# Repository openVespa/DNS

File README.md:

A wifi based EGT, CHT, RPM, Speed monitor board. Works on 6vac and 12vac systems. No need for a battery. It works with iOS and android, or really anything with wifi. The goal is to keep the size reasonable and the total build price under $25. It is based around the ESP8266 wifi SoC. RPM is calculated off the AC from the stator, using an NCV1124 for zero crossing. The EGT is a Ktype thermocouple and the CHT is a TrailTech. The EGT and CHT signals are converted using an ADS1120 ADC SPI device. To make it easy to modify, I'm doing all the firmware in Arduino.

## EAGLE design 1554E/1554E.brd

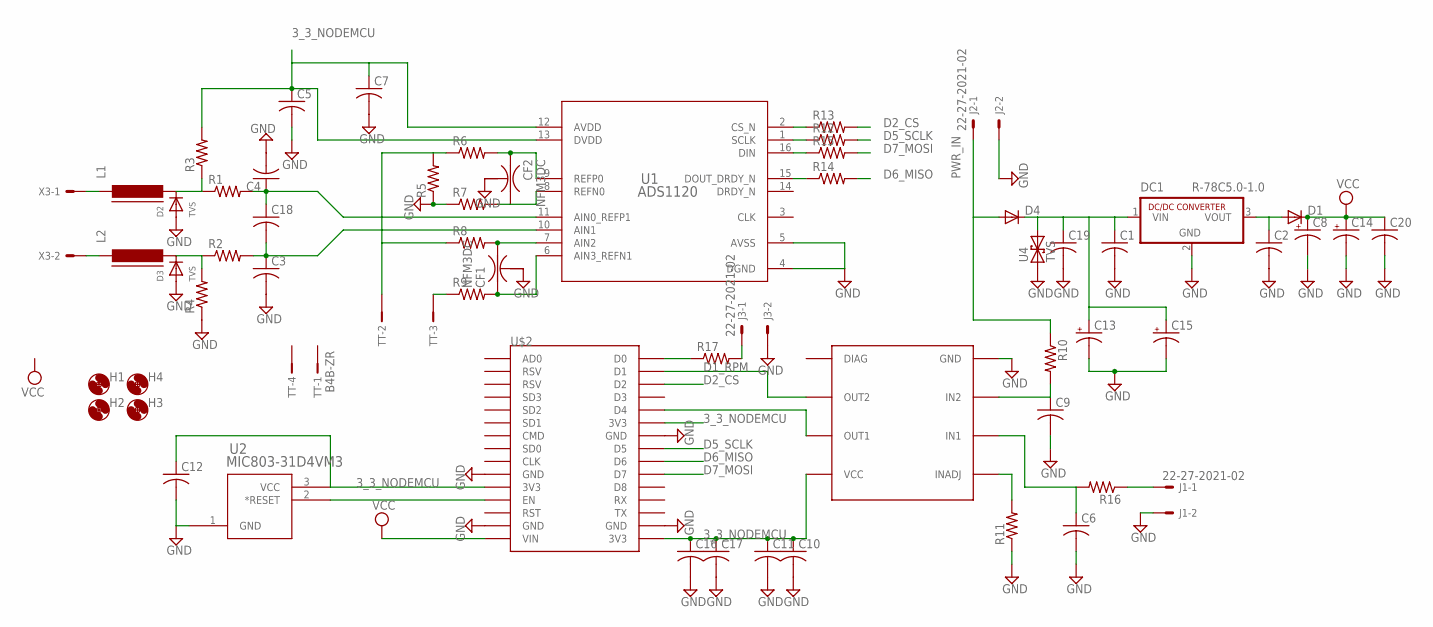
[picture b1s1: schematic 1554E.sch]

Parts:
C1, C2, C3, C4, C5, C6, C7, C9, C10, C11, C12, C18: C-USC0805K; C0805K
C8, C13, C14: CPOL-USE2.5-5; E2,5-5
C15: CPOL-USE7.5-16; E7,5-16
C16, C17, C19, C20: C-USC1206K; C1206K
CF1, CF2: NFM3DC
D1, D4: DIODE-DO-214AC; DO-214AC
D2, D3: TVS; SOD-323F
DC1: R-78C5.0-1.0; SIP3
H1, H2, H3, H4: MOUNT-HOLE2.8; 2,8
J1, J2, J3: 22-27-2021-02; 6410-02
L1, L2: FERRITE-0805; FB805
R1, R2, R3, R4, R5, R6, R7, R8, R9, R10, R11, R12, R13, R14, R15, R16, R17: R-US_R0805W; R0805W
TT: B4B-ZR
U1: ADS1120; PW0016A_N
U2: MIC803-31D4VM3; SOT-23_M3
U4: TVS; SMA-DIODE
U$1: NCV1124; TESTER
U$2: ESP12E_DEVKIT
X3: 22-23-2021; MPN 22-23-2021

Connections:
3_3_NODEMCU: C5.1, C7.1, C10.1, C11.1, C12.1, C16.1, C17.1, R3.2, U1.12 (AVDD), U1.13 (DVDD), U2.3 (VCC), U$1.VCC, U$2.3V3@0 (3V3), U$2.3V3@1 (3V3), U$2.3V3@2 (3V3)
D1_RPM: U$1.OUT2, U$2.D1
D2_CS: R13.2, U$2.D2
D5_SCLK: R12.2, U$2.D5
D6_MISO: R14.2, U$2.D6
D7_MOSI: R15.2, U$2.D7
GND: C1.2, C2.2, C3.2, C4.2, C5.2, C6.2, C7.2, C8.-, C9.2, C10.2, C11.2, C12.2, C13.-, C14.-, C15.-, C16.2, C17.2, C19.2, C20.2, CF1.2@1 (2), CF2.2@1 (2), D2.A, D3.A, DC1.2 (GND), J1.2, J2.2, J3.2, R4.1, R5.1, R7.1, R11.1, U1.4 (DGND), U1.5 (AVSS), U2.1 (GND), U4.A (1), U$1.GND, U$2.GND@0 (GND), U$2.GND@1 (GND), U$2.GND@2 (GND), U$2.GND@3 (GND)
unnamed: L1.1, X3.1
unnamed: C2.1, D1.A, DC1.3 (VOUT)
unnamed: CF1.1, R9.2, U1.6 (AIN3_REFN1)
unnamed: CF2.3, R7.2, U1.8 (REFN0)
unnamed: D3.C, L2.2, R2.1, R4.2
unnamed: C4.1, C18.1, R1.2, U1.11 (AIN0_REFP1)
unnamed: C3.1, C18.2, R2.2, U1.10 (AIN1)
unnamed: D2.C, L1.2, R1.1, R3.1
unnamed: R11.2, U$1.INADJ
unnamed: CF2.1, R6.2, U1.9 (REFP0)
unnamed: U2.2 (*RESET), U$2.EN
unnamed: CF1.3, R8.2, U1.7 (AIN2)
unnamed: C9.1, R10.2, U$1.IN2
unnamed: L2.1, X3.2
unnamed: R9.1, TT.3
unnamed: R13.1, U1.2 (CS_N)
unnamed: J1.1, R16.1
unnamed: R14.1, U1.15 (DOUT_DRDY_N)
unnamed: R15.1, U1.16 (DIN)
unnamed: R12.1, U1.1 (SCLK)
unnamed: C1.1, C13.+, C15.+, C19.1, D4.C, DC1.1 (VIN), U4.C (2)
unnamed: C6.1, R16.2, U$1.IN1
unnamed: U$1.OUT1, U$2.D4
unnamed: R17.1, U$2.D0
unnamed: J3.1, R17.2
PWR_IN: D4.A, J2.1, R10.1
REF_P: R5.2, R6.1, R8.1, TT.2
VCC: C8.+, C14.+, C20.1, D1.C, U$2.VIN

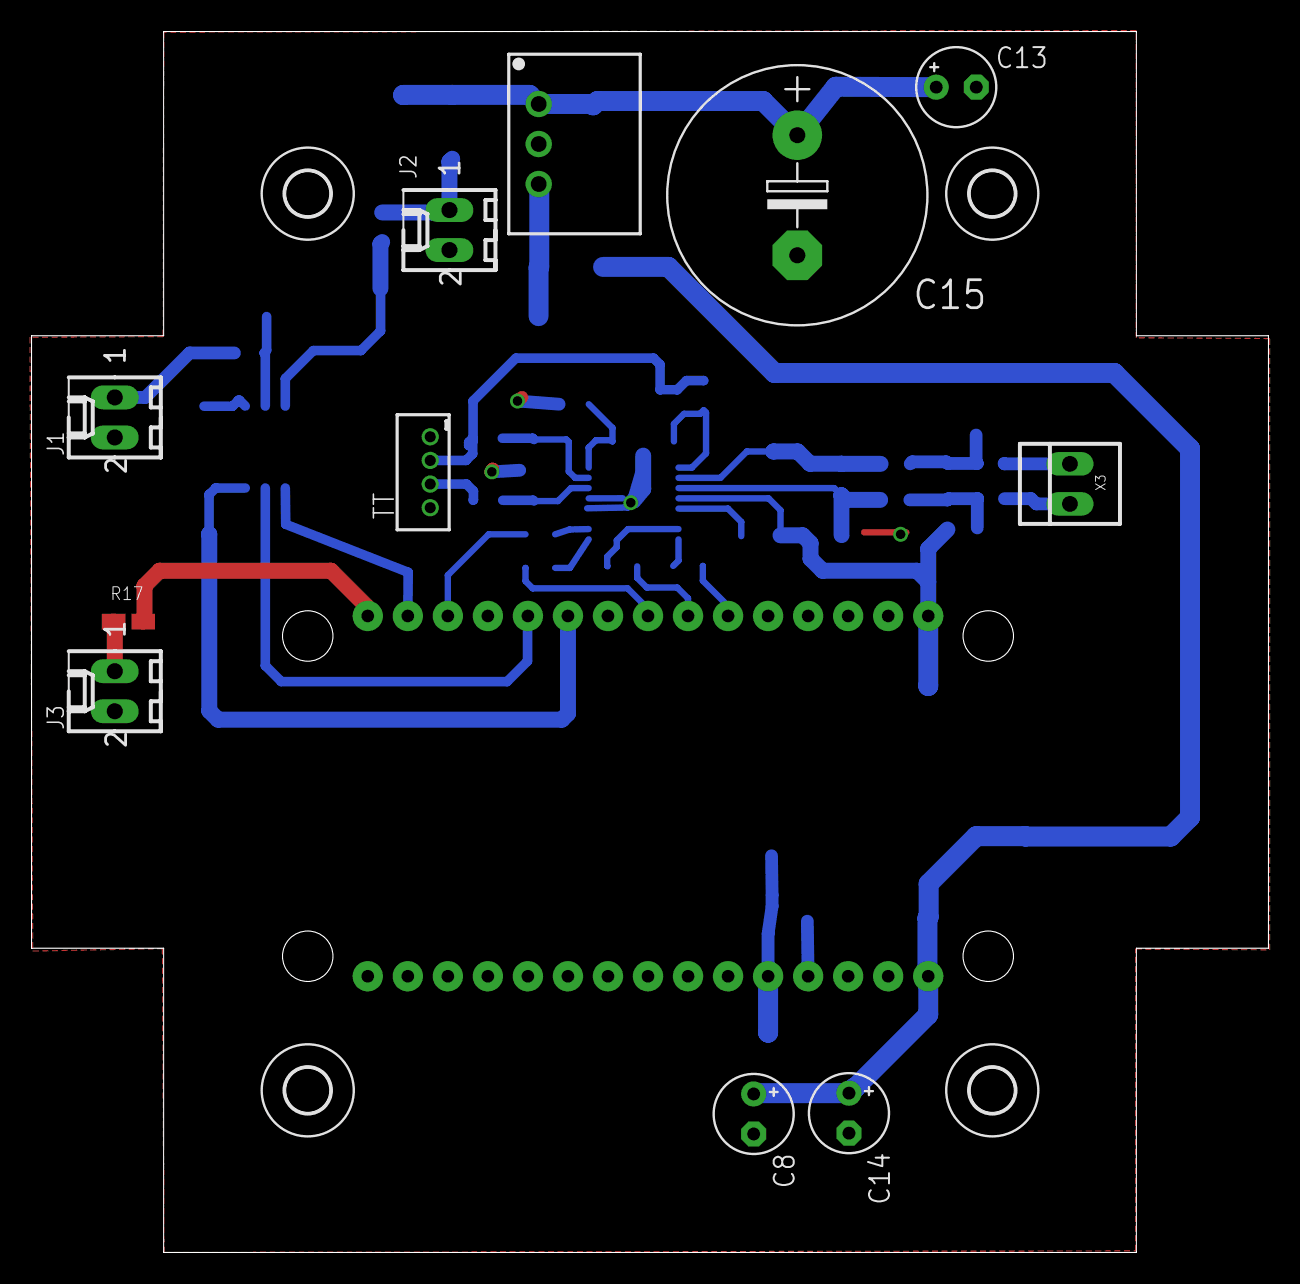
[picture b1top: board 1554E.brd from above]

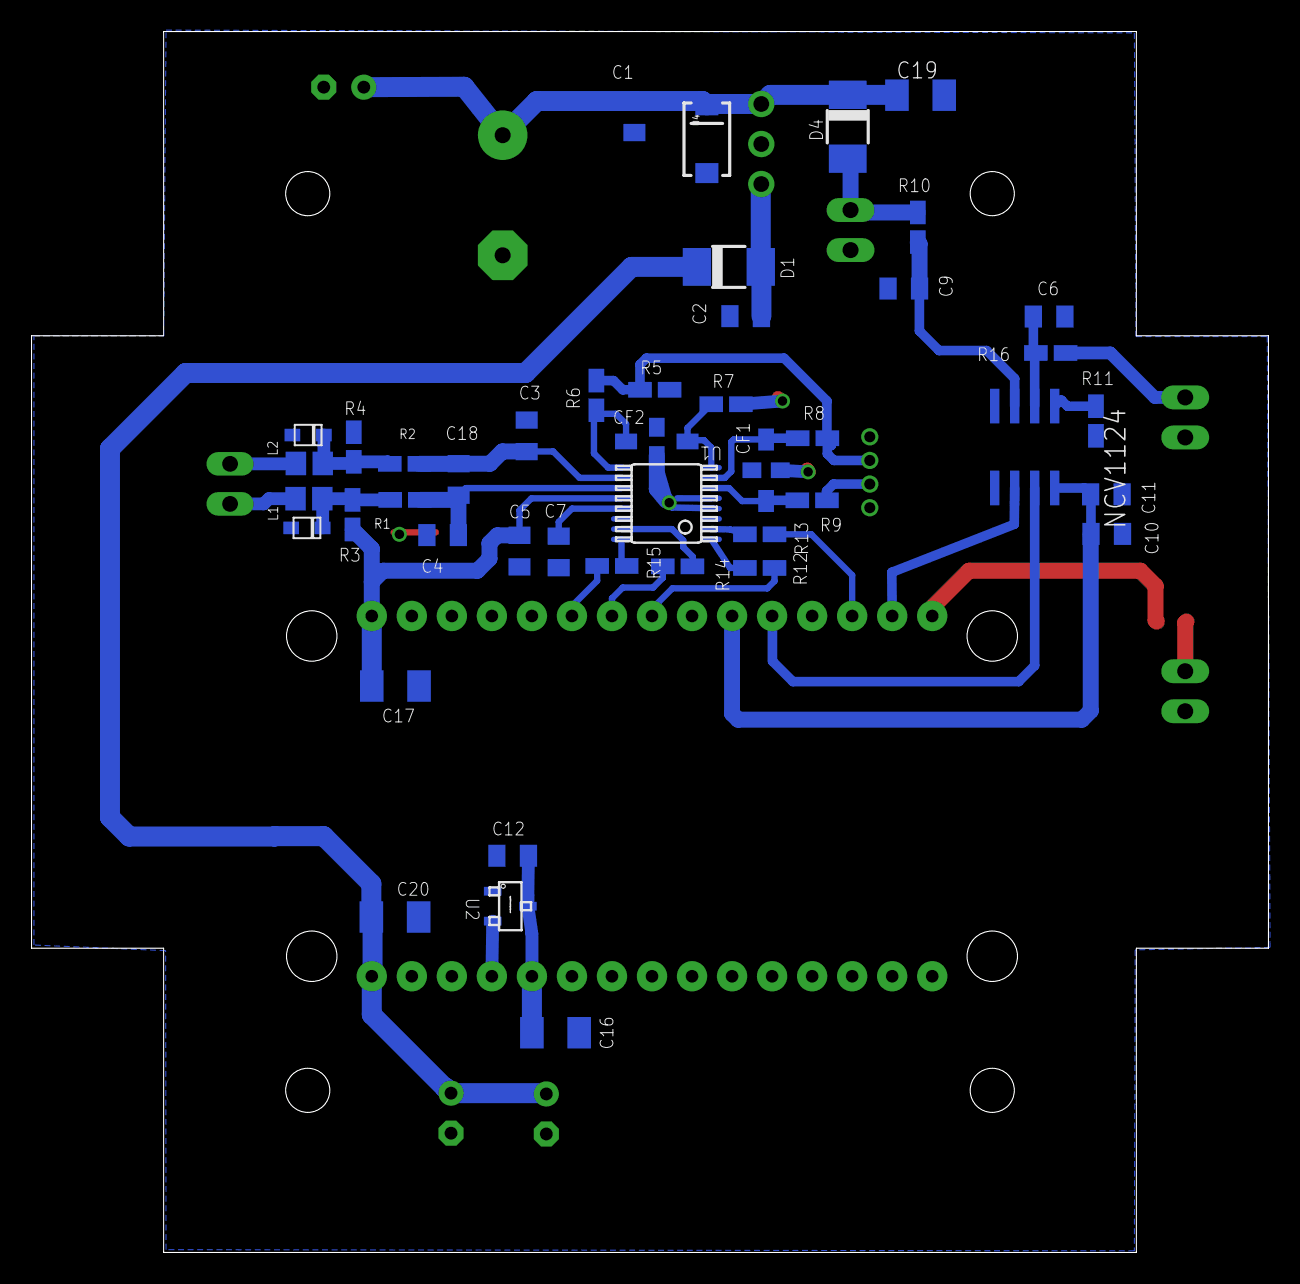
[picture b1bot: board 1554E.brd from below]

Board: 2 copper layers, 78.5 x 77.5 mm, 60 parts (44 on the bottom side), 35 nets.

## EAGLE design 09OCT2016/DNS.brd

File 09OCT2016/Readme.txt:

This is just some early schematic capture and layout work. I also added the arduino code that was written for the protoype. In the protoype I used a different thermocouple amplifer for EGT and the onboard ADC for the CHT. In the final version, I'll do both using the ADS1120.

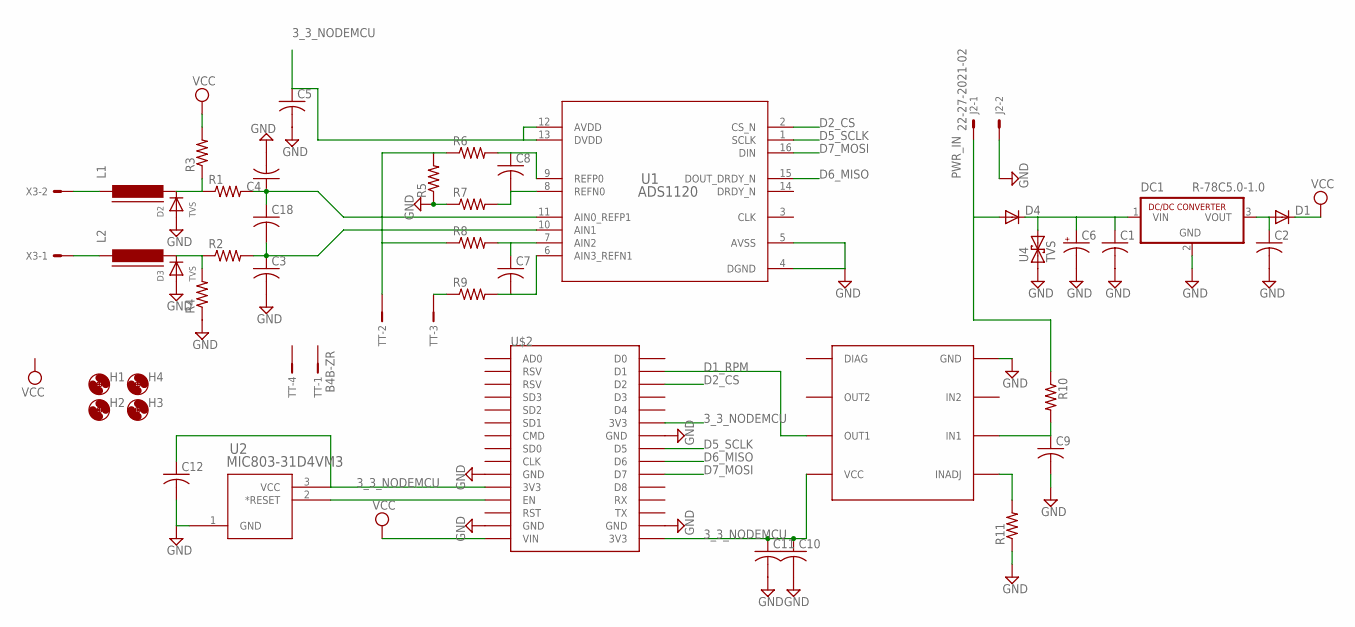
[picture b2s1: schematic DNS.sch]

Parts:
C1, C2, C3, C4, C5, C7, C8, C9, C10, C11, C12, C18: C-USC0805; C0805
C6: CPOL-USE5-10.5; E5-10,5
D1, D4: DIODE-DO-214AC; DO-214AC
D2, D3: TVS; SOD-323F
DC1: R-78C5.0-1.0; SIP3
H1, H2, H3, H4: MOUNT-HOLE2.8; 2,8
J2: 22-27-2021-02; 6410-02
L1, L2: FERRITE-0805; FB805
R1, R2, R3, R4, R5, R6, R7, R8, R9, R10, R11: R-US_R0805W; R0805W
TT: B4B-ZR
U1: ADS1120; PW0016A_N
U2: MIC803-31D4VM3; SOT-23_M3
U4: TVS; SMA-DIODE
U$1: NCV1124; TESTER
U$2: ESP12E_DEVKIT
X3: 22-23-2021; MPN 22-23-2021

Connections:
3_3_NODEMCU: C10.1, C11.1, C12.1, U2.3 (VCC), U$1.VCC, U$2.3V3@0 (3V3), U$2.3V3@1 (3V3), U$2.3V3@2 (3V3)
D1_RPM: U$1.OUT1, U$2.D1
D2_CS: U1.2 (CS_N), U$2.D2
D5_SCLK: U1.1 (SCLK), U$2.D5
D6_MISO: U1.15 (DOUT_DRDY_N), U$2.D6
D7_MOSI: U1.16 (DIN), U$2.D7
GND: C1.2, C2.2, C3.2, C4.2, C5.2, C6.-, C9.2, C10.2, C11.2, C12.2, D2.A, D3.A, DC1.2 (GND), J2.2, R4.1, R5.1, R7.1, R11.1, U1.4 (DGND), U1.5 (AVSS), U2.1 (GND), U4.A (1), U$1.GND, U$2.GND@0 (GND), U$2.GND@1 (GND), U$2.GND@2 (GND), U$2.GND@3 (GND)
unnamed: C1.1, C6.+, D4.C, DC1.1 (VIN), U4.C (2)
unnamed: C2.1, D1.A, DC1.3 (VOUT)
unnamed: C7.2, R9.2, U1.6 (AIN3_REFN1)
unnamed: C8.2, R7.2, U1.8 (REFN0)
unnamed: D3.C, L2.2, R2.1, R4.2
unnamed: C4.1, C18.1, R1.2, U1.11 (AIN0_REFP1)
unnamed: C3.1, C18.2, R2.2, U1.10 (AIN1)
unnamed: D2.C, L1.2, R1.1, R3.1
unnamed: R11.2, U$1.INADJ
unnamed: C8.1, R6.2, U1.9 (REFP0)
unnamed: U2.2 (*RESET), U$2.EN
unnamed: C7.1, R8.2, U1.7 (AIN2)
unnamed: C9.1, R10.2, U$1.IN1
unnamed: L2.1, X3.1
unnamed: R9.1, TT.3
unnamed: L1.1, X3.2
unnamed: C5.1, U1.12 (AVDD), U1.13 (DVDD)
PWR_IN: D4.A, J2.1, R10.1
REF_P: R5.2, R6.1, R8.1, TT.2
VCC: D1.C, R3.2, U$2.VIN

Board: 2 copper layers, 43 parts (8 on the bottom side), 27 nets, no tracks yet.

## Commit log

2016-10-11 Create Temp

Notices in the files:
parts and their libraries:
SparkFun-DiscreteSemi: Licensing: CC v3.0 Share-Alike You are welcome to use this library for commercial purposes.
MIC803: Copyright (C) 2015 Accelerated Designs. All rights reserved
COPYRIGHT: Copyright (C) 2015 Accelerated Designs. All rights reserved
